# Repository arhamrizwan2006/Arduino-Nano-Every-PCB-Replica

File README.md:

# Arduino Nano Every - Chip-Level PCB Replica

A full chip-level PCB replica of the Arduino Nano Every (ABX00028), designed from scratch in KiCad 10 - complete schematic, custom component creation, auto+manual routing, and manufacturing-ready output.

## Overview
This project replicates the official Arduino Nano Every board at the component level, rebuilding its schematic and PCB layout across five sub-circuits, verifying the design with zero DRC (Design Rule Check) errors, and generating full manufacturing files (Gerbers, drill files, BOM).

## Sub-Circuits Designed
1. MP2322 Power Regulator - voltage regulation circuit
2. ATmega4809 MCU - main microcontroller circuit
3. ATSAMD11D14A USB Bridge - USB-to-serial bridge controller
4. USB Micro-B Connector - power/data input
5. I/O Headers - 2x 15-pin connectors for digital/analog I/O

## PCB Layout

## 3D Renders
Top and Bottom renders available in images/pcb_3d_top.png and images/pcb_3d_bottom.png

## Schematic
Full schematic available as PDF: images/schematic_overview.pdf

## Design Process
- Schematic captured across 5 sub-circuits in KiCad 10
- Custom footprint and 3D model created for the MP2322 regulator (not available in standard libraries) - see components/ folder
- PCB layout with auto-routing via FreeRouting v2.2.4, followed by manual trace completion for optimization
- Design Rule Check (DRC) run to zero errors before finalizing
- Full manufacturing output generated: Gerbers, drill files (PTH/NPTH), and Bill of Materials

## Repository Structure
kicad_project/
|-- NanoEvery_Replica.kicad_pro     - KiCad project file
|-- NanoEvery_Replica.kicad_sch     - Schematic
|-- NanoEvery_Replica.kicad_pcb     - PCB layout
|-- gerber_files/                    - Manufacturing-ready Gerber + drill files
|-- bom/                              - Bill of Materials (CSV)
|-- components/                       - Custom footprint, symbol, and 3D model (MP2322)
|-- images/                           - Schematic, PCB layout, and 3D render exports

## Bill of Materials
Full BOM available in bom/NanoEvery_Replica.csv

## Manufacturing Files
Gerber and drill files ready for fabrication are in gerber_files/

## What I Learned
- Full-board schematic design across multiple interconnected sub-circuits
- Creating custom footprints and 3D models for components not in standard libraries
- PCB auto-routing (FreeRouting) combined with manual routing optimization
- Design Rule Checking and achieving a fully clean (zero-error) layout
- Generating complete, fabrication-ready manufacturing outputs (Gerbers, drill files, BOM)

## Future Improvements
- Order and assemble a physical prototype to validate the design
- Add functional testing documentation once built

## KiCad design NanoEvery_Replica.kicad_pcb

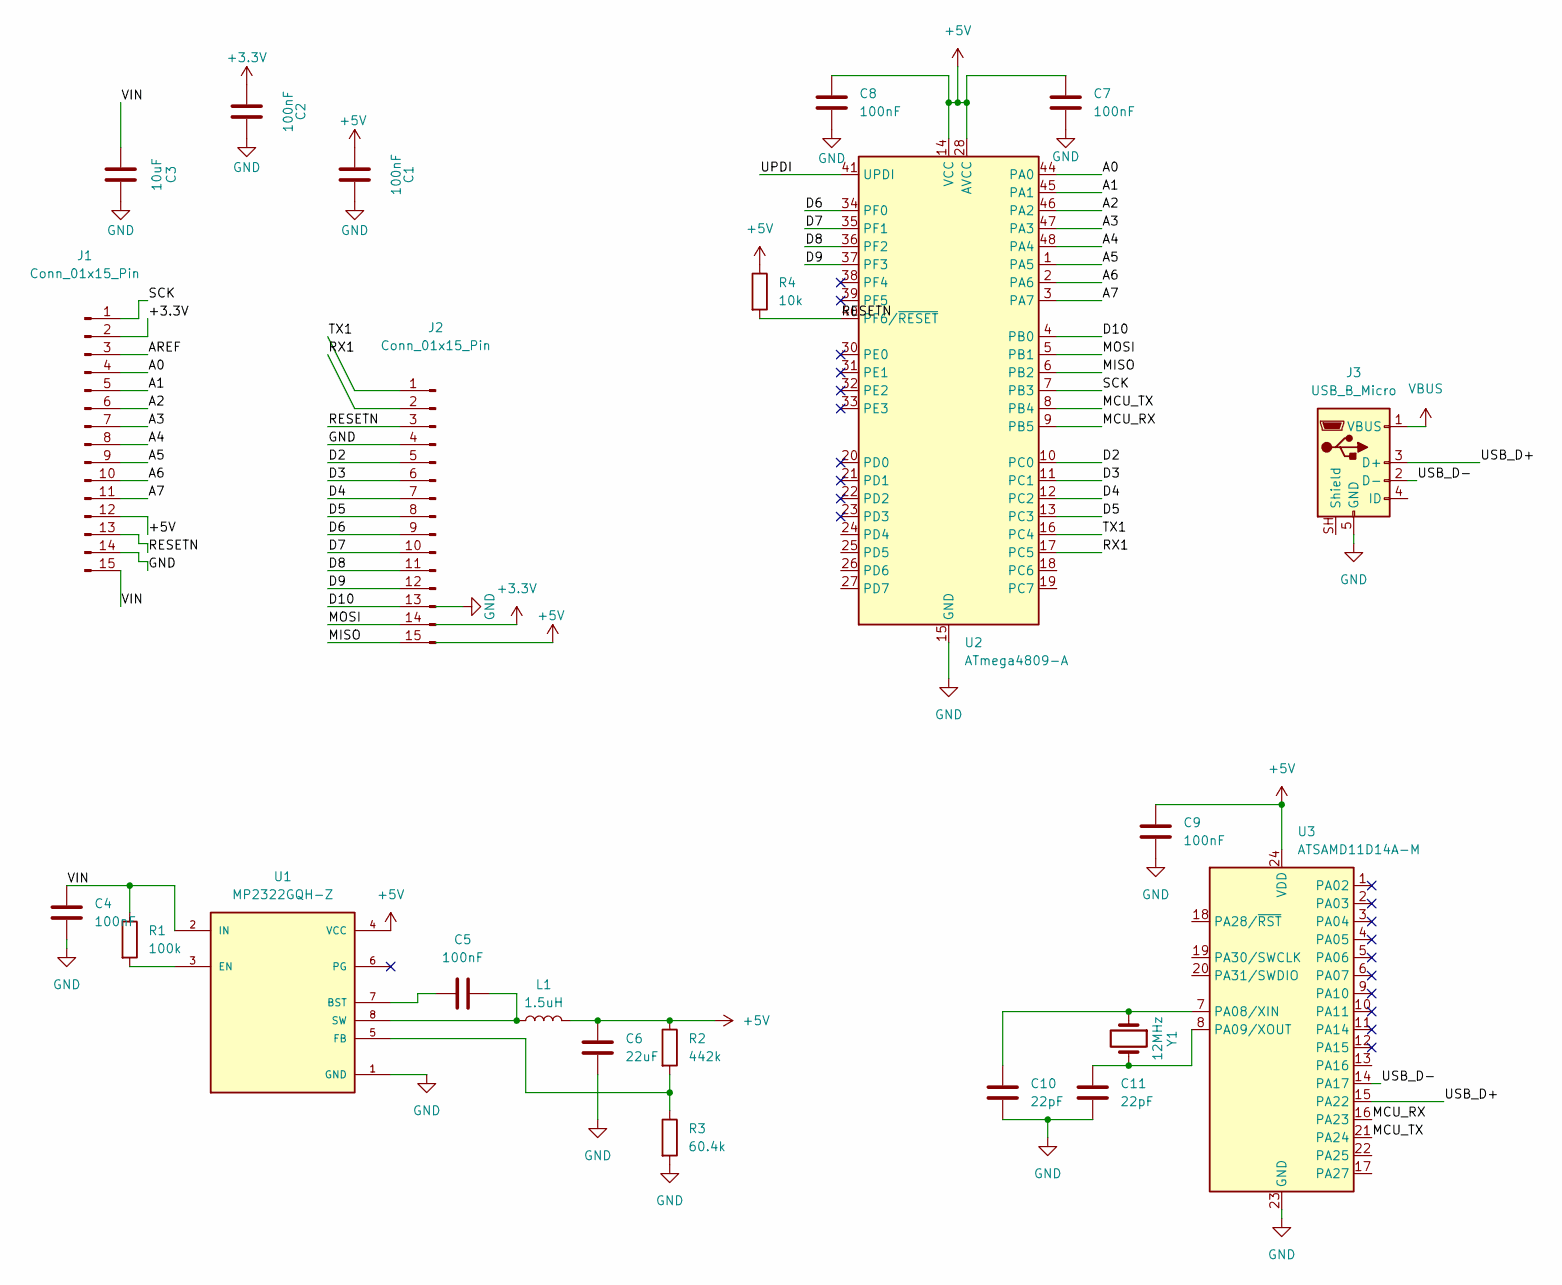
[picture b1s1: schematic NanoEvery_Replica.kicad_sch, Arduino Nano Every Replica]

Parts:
C1, C2, C4, C5, C7, C8, C9: 100nF; C_0402_1005Metric
C3: 10uF; C_0402_1005Metric
C6: 22uF; C_0805_2012Metric
C10, C11: 22pF; C_0402_1005Metric
J1, J2: Conn_01x15_Pin; PinHeader_1x15_P2.54mm_Vertical
J3: USB_B_Micro; USB_Micro-B_Amphenol_10118194_Horizontal
L1: 1.5uH; L_0603_1608Metric
R1: 100k; R_0402_1005Metric
R2: 442k; R_0402_1005Metric
R3: 60.4k; R_0402_1005Metric
R4: 10k; R_0402_1005Metric
U1: MP2322GQH-Z; CONV_MP2322GQH-Z; PARTREV 1.01; DigiKey_Part_Number 1589-MP2322GQH-ZCT-ND
U2: ATmega4809-A; TQFP-48_7x7mm_P0.5mm
U3: ATSAMD11D14A-M; QFN-24-1EP_4x4mm_P0.5mm_EP2.6x2.6mm
Y1: 12MHz; Crystal_SMD_3225-4Pin_3.2x2.5mm

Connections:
+3.3V: C2.2, J1.2
+5V: C1.1, C6.1, C7.1, C8.1, C9.1, J1.12, L1.2, R2.1, R4.1, U1.4 (VCC), U2.14 (VCC), U2.28 (AVCC), U2.42 (VCC), U3.24 (VDD)
/A0: J1.4, U2.44 (PA0)
/A1: J1.5, U2.45 (PA1)
/A2: J1.6, U2.46 (PA2)
/A3: J1.7, U2.47 (PA3)
/A4: J1.8, U2.48 (PA4)
/A5: J1.9, U2.1 (PA5)
/A6: J1.10, U2.2 (PA6)
/A7: J1.11, U2.3 (PA7)
/AREF: J1.3
/D2: J2.5, U2.10 (PC0)
/D3: J2.6, U2.11 (PC1)
/D4: J2.7, U2.12 (PC2)
/D5: J2.8, U2.13 (PC3)
/D6: J2.9, U2.34 (PF0)
/D7: J2.10, U2.35 (PF1)
/D8: J2.11, U2.36 (PF2)
/D9: J2.12, U2.37 (PF3)
/D10: J2.13, U2.4 (PB0)
/MCU_RX: U2.9 (PB5), U3.16 (PA23)
/MCU_TX: U2.8 (PB4), U3.21 (PA24)
/MISO: J2.15, U2.6 (PB2)
/MOSI: J2.14, U2.5 (PB1)
/RESETN: J1.13, J2.3, R4.2, U2.40 (PF6/~RESET)
/RX1: J2.2, U2.17 (PC5)
/SCK: J1.1, U2.7 (PB3)
/TX1: J2.1, U2.16 (PC4)
/UPDI: U2.41 (UPDI)
/USB_D+: J3.3 (D+), U3.15 (PA22)
/USB_D-: J3.2 (D-), U3.14 (PA17)
/VIN: C3.2, C4.1, J1.15, R1.1, U1.2 (IN)
GND: C1.2, C2.1, C3.1, C4.2, C6.2, C7.2, C8.2, C9.2, C10.2, C11.2, J1.14, J2.4, J3.5 (GND), R3.2, U1.1 (GND), U2.15 (GND), U2.29 (GND), U2.43 (GND), U3.23 (GND)
unnamed: C5.1, U1.7 (BST)
unnamed: R1.2, U1.3 (EN)
unnamed: R2.2, R3.1, U1.5 (FB)
unnamed: C5.2, L1.1, U1.8 (SW)
unnamed: C10.1, U3.7 (PA08/XIN), Y1.1
unnamed: C11.1, U3.8 (PA09/XOUT), Y1.2
VBUS: J3.1 (VBUS)

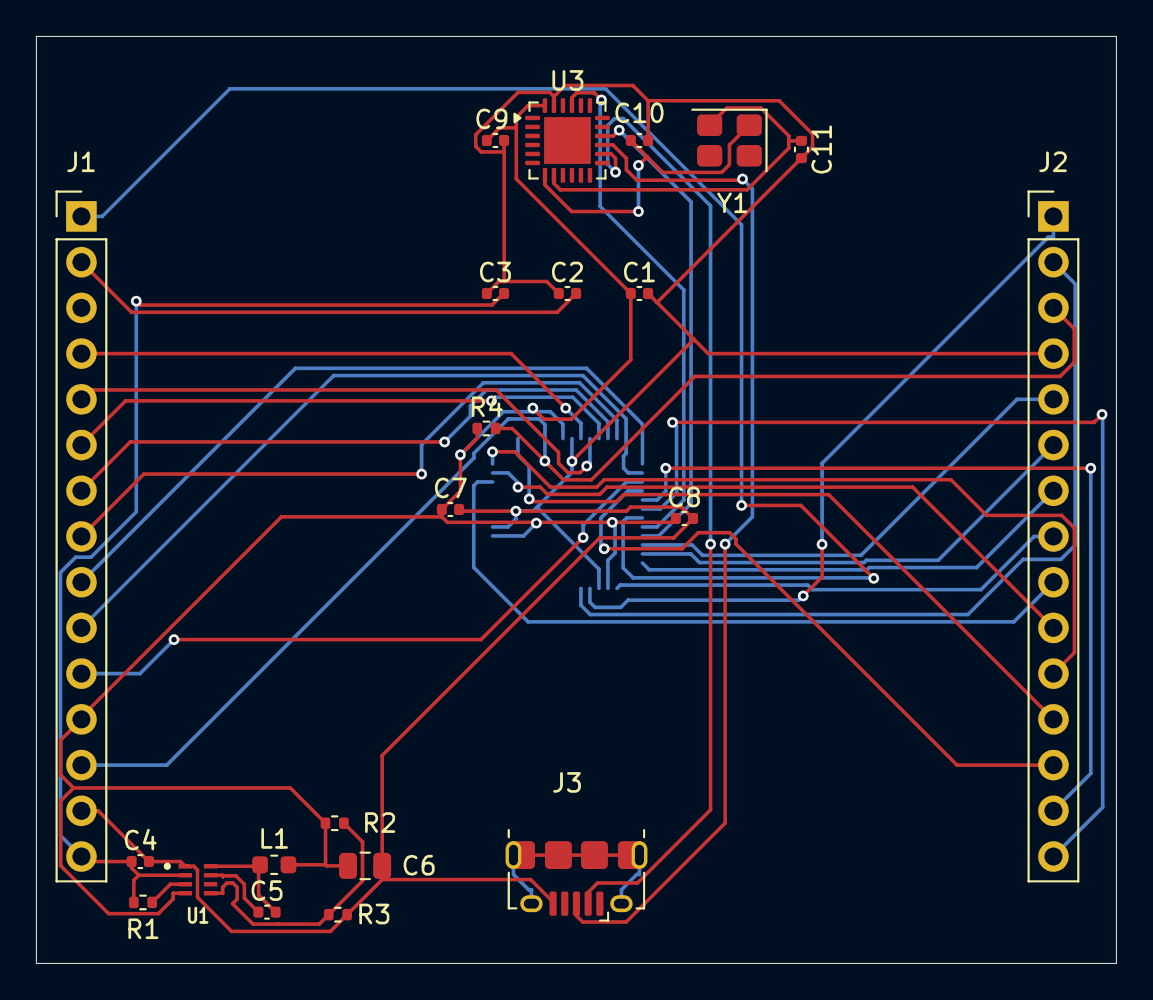
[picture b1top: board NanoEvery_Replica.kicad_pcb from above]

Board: 2 copper layers, 60.0 x 51.5 mm, 23 parts (1 on the bottom side), 37 nets.
